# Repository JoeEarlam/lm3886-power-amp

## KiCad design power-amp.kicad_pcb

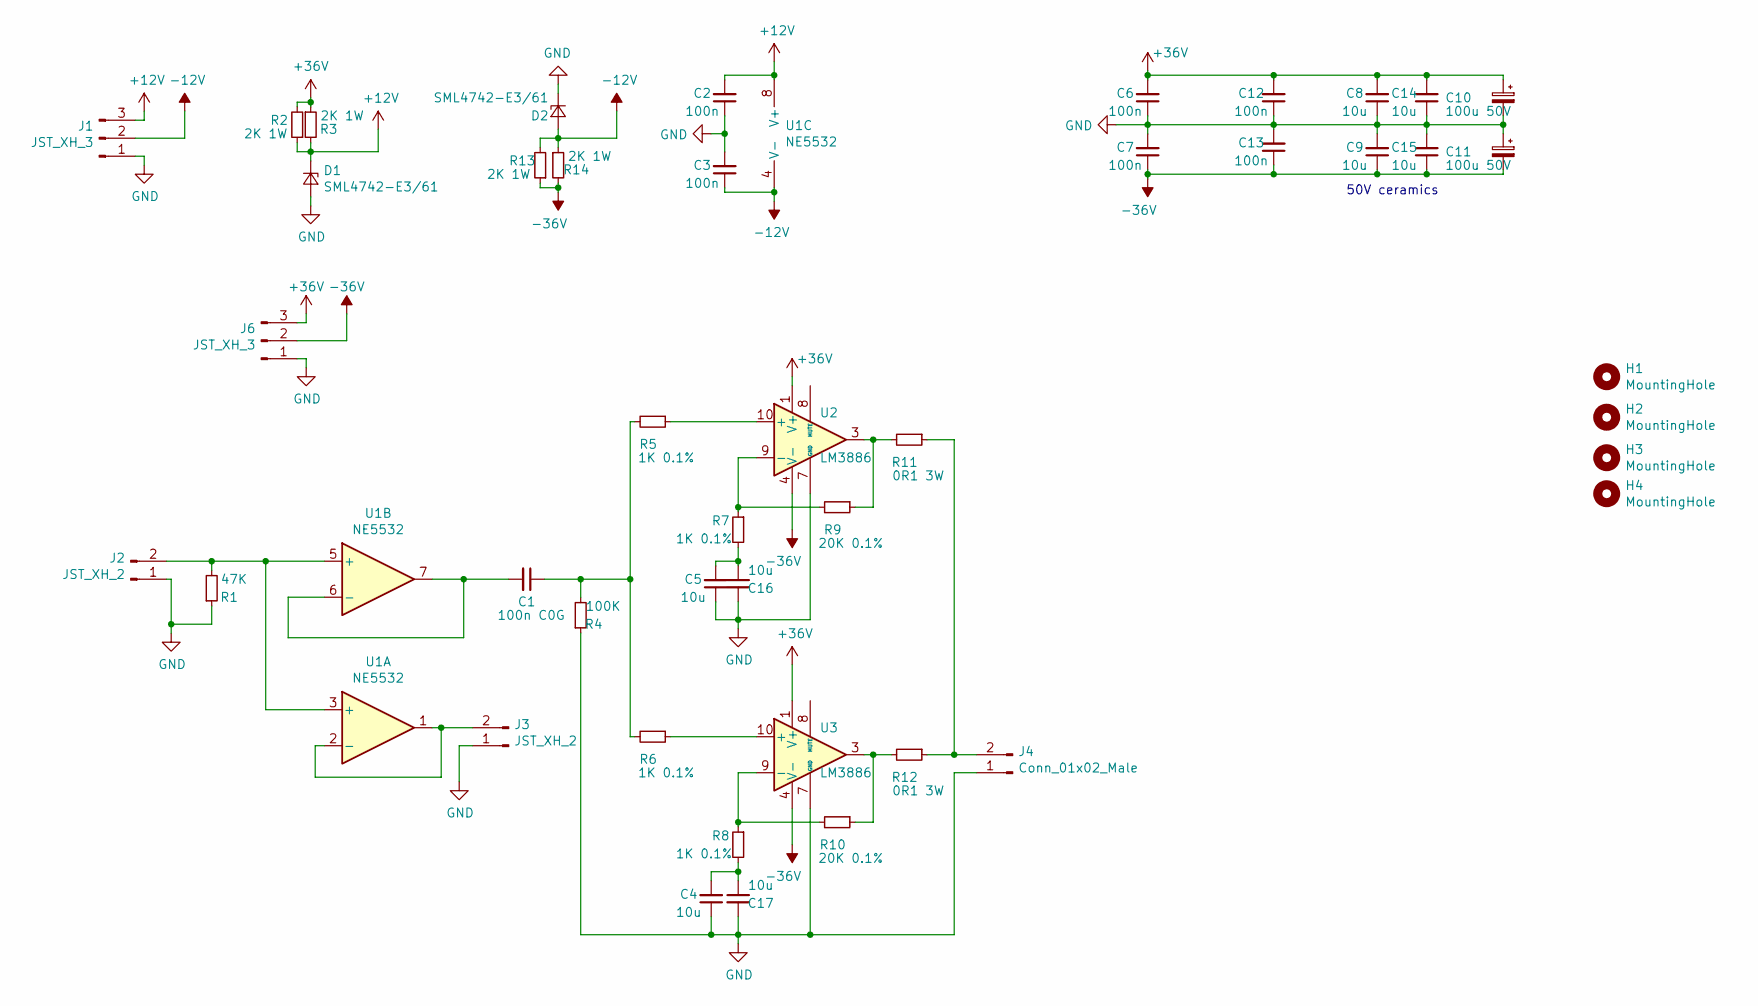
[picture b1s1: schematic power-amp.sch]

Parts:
C1: 100n C0G; C_1206_3216Metric; Part Number CGA5L2C0G1H104J160AA
C2, C3, C6, C7, C12, C13: 100n; C_0805_2012Metric
C4, C5, C8, C9, C14, C15, C16, C17: 10u; C_1206_3216Metric
C10, C11: 100u 50V; CP_Elec_10x10; Part Number A767MU107M1HLAE027
D1, D2: SML4742-E3/61; D_SMA
H1, H2, H3, H4: MountingHole; MountingHole_3.2mm_M3
J1: JST_XH_3; JST_XH_B3B-XH-A_1x03_P2.50mm_Vertical
J2, J3: JST_XH_2; JST_XH_B2B-XH-A_1x02_P2.50mm_Vertical
J4: Conn_01x02_Male; PhoenixContact_MSTBA_2,5_2-G_1x02_P5.00mm_Horizontal
J6: JST_XH_3; PhoenixContact_MSTBA_2,5_3-G_1x03_P5.00mm_Horizontal
R1: 47K; R_0805_2012Metric
R2, R3, R13, R14: 2K 1W; R_1206_3216Metric
R4: 100K; R_0805_2012Metric
R5, R6, R7, R8: 1K 0.1%; R_0805_2012Metric
R9, R10: 20K 0.1%; R_0805_2012Metric
R11, R12: 0R1 3W; R_2512_6332Metric; Part Number CRA2512-FZ-R100ELF
U1: NE5532; SOIC-8_3.9x4.9mm_P1.27mm
U2, U3: LM3886; TO-220-11_P3.4x5.08mm_StaggerOdd_Lead4.85mm_Vertical

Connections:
+12V: C2.2, D1.1 (K), J1.3, R2.1, R3.2, U1.8 (V+)
+36V: C6.2, C8.2, C10.1, C12.2, C14.2, J6.3, R2.2, R3.1, U2.1 (V+), U2.5 (V+), U3.1 (V+), U3.5 (V+)
-12V: C3.1, D2.2 (A), J1.2, R13.2, R14.1, U1.4 (V-)
-36V: C7.1, C9.1, C11.2, C13.1, C15.1, J6.2, R13.1, R14.2, U2.4 (V-), U3.4 (V-)
GND: C2.1, C3.2, C4.1, C5.1, C6.1, C7.2, C8.1, C9.2, C10.2, C11.1, C12.1, C13.2, C14.1, C15.2, C16.2, C17.2, D1.2 (A), D2.1 (K), J1.1, J2.1, J3.1, J4.1, J6.1, R1.1, R4.1, U2.7 (GND), U3.7 (GND)
unnamed: C1.1, R4.2, R5.2, R6.2
unnamed: C1.2, U1.6 (-), U1.7
unnamed: C5.2, C16.1, R7.2
unnamed: C4.2, C17.1, R8.2
unnamed: J2.2, R1.2, U1.3 (+), U1.5 (+)
unnamed: J3.2, U1.1, U1.2 (-)
unnamed: J4.2, R11.1, R12.1
unnamed: R5.1, U2.10 (+)
unnamed: R6.1, U3.10 (+)
unnamed: R7.1, R9.2, U2.9 (-)
unnamed: R10.1, R12.2, U3.3
unnamed: R8.1, R10.2, U3.9 (-)
unnamed: R9.1, R11.2, U2.3

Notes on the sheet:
50V ceramics

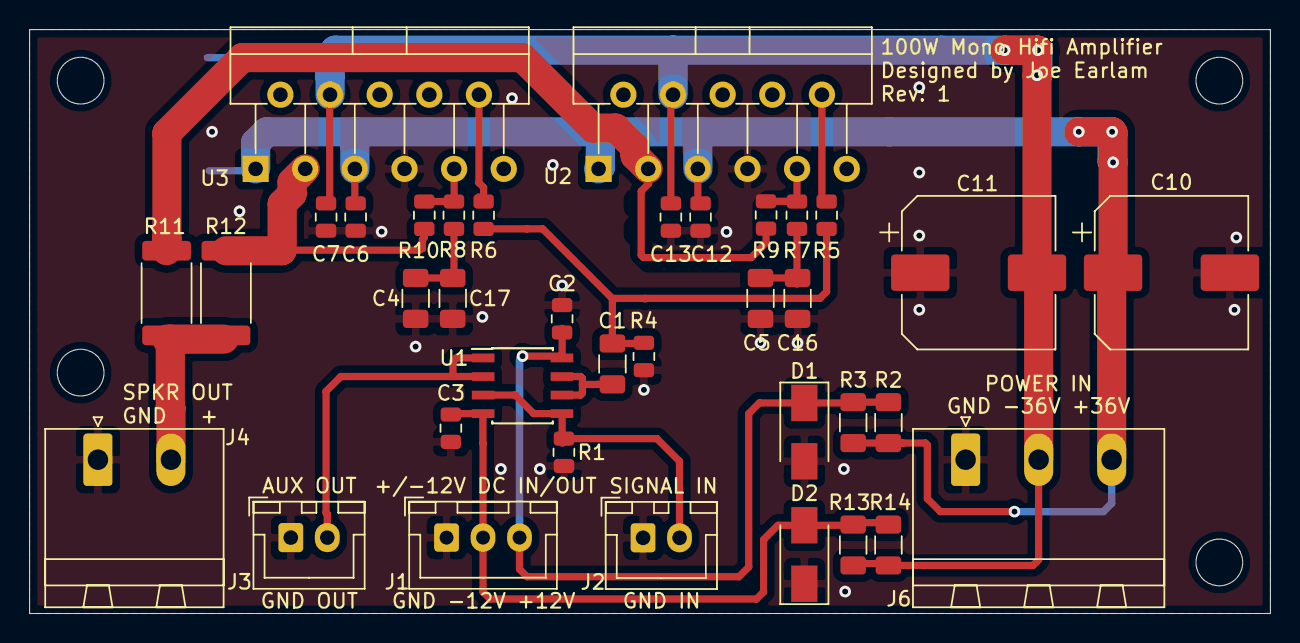
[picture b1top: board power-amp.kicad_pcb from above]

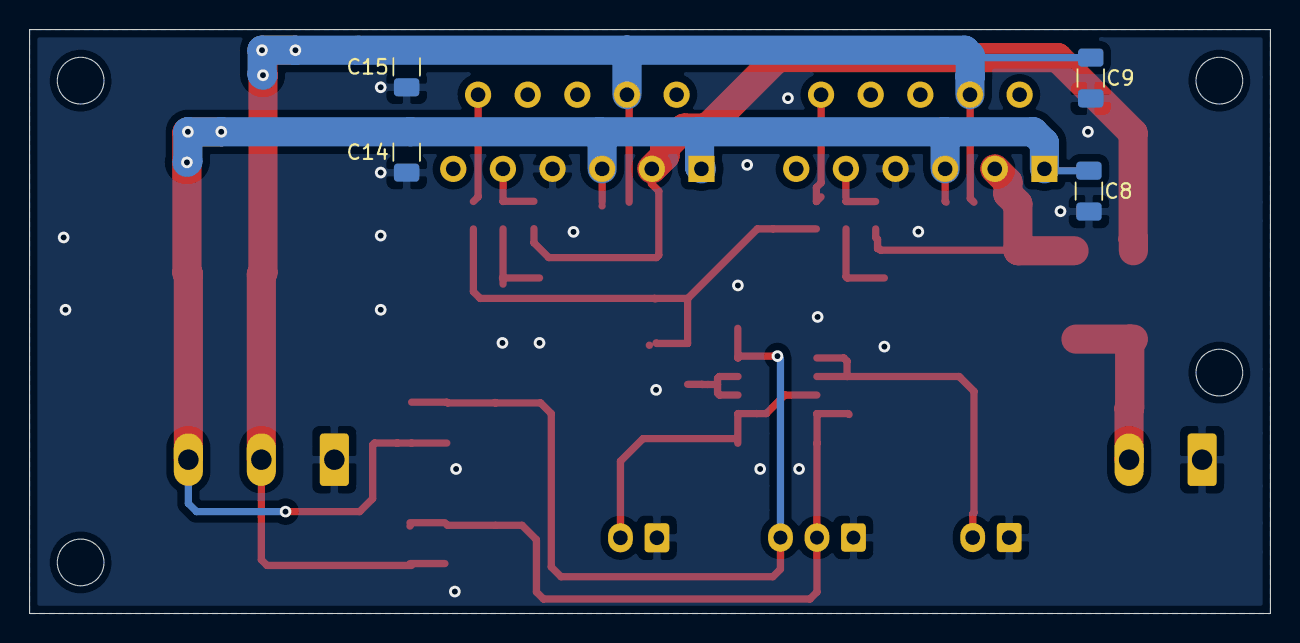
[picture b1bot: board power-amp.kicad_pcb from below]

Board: 2 copper layers, 85.0 x 40.0 mm, 45 parts (4 on the bottom side), 18 nets.

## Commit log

2019-05-28 fixed resistor values
